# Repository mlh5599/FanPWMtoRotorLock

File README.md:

# FanPWMtoRotorLock
Utilizes a missing pulse detector based on the circuitry [here](https://www.falstad.com/circuit/e-555missing.html) to convert the output from a 12v PWM fan to a rotor lock detector signal.

## BOM

- 1 10uf Capacitor SMT 08051 
- Molex 022232031 Connector
- 1 JST-PH2.0MM Connector
- 1 MMBT2222A-7-F SOT-23 NPN Transistor
- 1 MMBT2907ALT1G SOT-23 PNP Transistor
- 5 10K Ohm Restor SMT 0805
- 1 100 Ohm Resistor SMT 0805
- 1 NE555P SOIC-8 Timer

## Images

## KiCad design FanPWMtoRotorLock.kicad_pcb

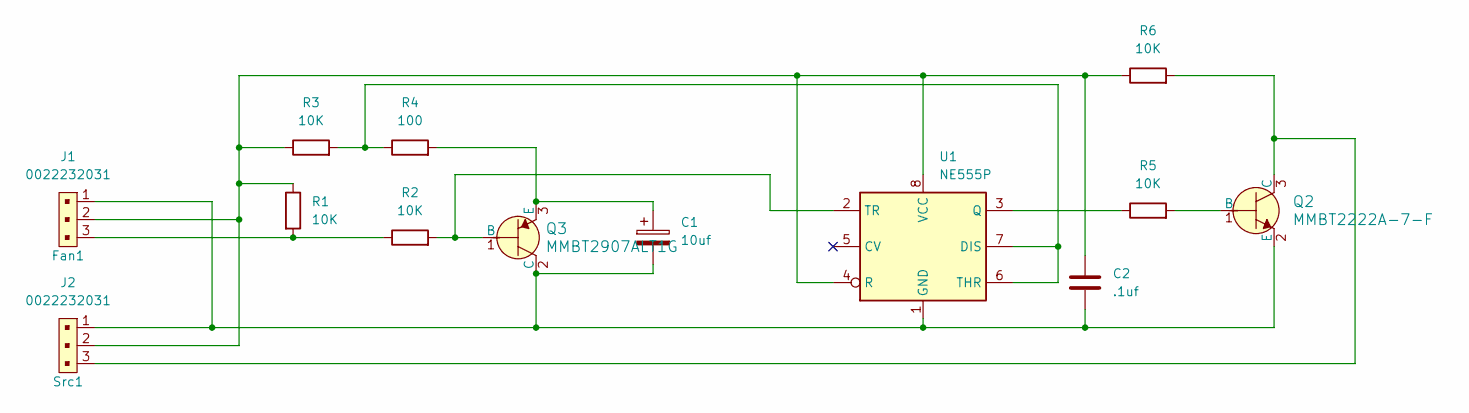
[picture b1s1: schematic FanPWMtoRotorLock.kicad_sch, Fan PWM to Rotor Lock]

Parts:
C1: 10uf; C_0805_2012Metric_Pad1.18x1.45mm_HandSolder
C2: .1uf; C_0805_2012Metric_Pad1.18x1.45mm_HandSolder
J1: 0022232031; PinHeader_1x3_P2.54mm_Drill1.02mm; MPN 0022232031; Digi-Key_PN WM4201-ND
J2: 0022232031; JST_PH_B3B-PH-K_1x03_P2.00mm_Vertical; MPN 0022232031; Digi-Key_PN WM4201-ND
Q2: MMBT2222A-7-F; SOT-23-3; MPN MMBT2222A-7-F; Digi-Key_PN MMBT2222A-FDICT-ND
Q3: MMBT2907ALT1G; SOT-23-3; MPN MMBT2907ALT1G; Digi-Key_PN MMBT2907ALT1GOSCT-ND
R1, R2, R3, R5, R6: 10K; R_0805_2012Metric_Pad1.20x1.40mm_HandSolder
R4: 100; R_0805_2012Metric_Pad1.20x1.40mm_HandSolder
U1: NE555P; SOIC-8_3.9x4.9mm_P1.27mm

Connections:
unnamed: J1.3, R1.2, R2.1
unnamed: Q2.1 (B), R5.2
unnamed: J2.3, Q2.3 (C), R6.2
unnamed: C1.2, C2.2, J1.1, J2.1, Q2.2 (E), Q3.2 (C), U1.1 (GND)
unnamed: Q3.1 (B), R2.2, U1.2 (TR)
unnamed: C1.1, Q3.3 (E), R4.2
unnamed: R3.2, R4.1, U1.6 (THR), U1.7 (DIS)
unnamed: R5.1, U1.3 (Q)
unnamed: C2.1, J1.2, J2.2, R1.1, R3.1, R6.1, U1.4 (R), U1.8 (VCC)

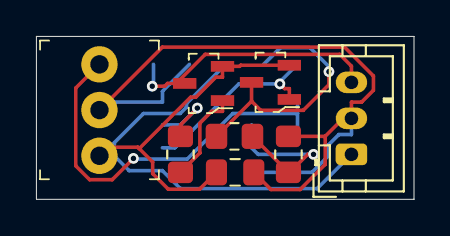
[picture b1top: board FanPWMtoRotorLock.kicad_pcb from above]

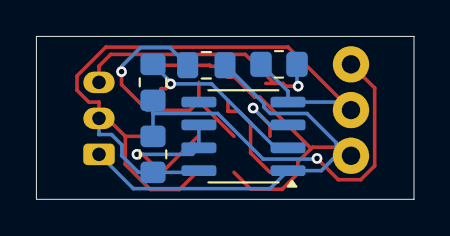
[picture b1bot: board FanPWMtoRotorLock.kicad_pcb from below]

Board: 2 copper layers, 21.0 x 9.0 mm, 13 parts (5 on the bottom side), 9 nets.

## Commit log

2024-10-23 Inital commit, schematic complete
2024-10-24 Inital board layout work
2024-10-24 Final board layout, update 3d models, update README.md
2024-10-24 Fix broken links in README.md
2024-10-24 Remove fabrication files from root project directory
2024-10-24 Update 3D models for SOT-23 packages
2024-10-27 Final layout, ready for manufacture
2024-10-28 Update readme with latest board image, fix formatting
2024-10-31 Added decoupling cap, shrunk board layout
